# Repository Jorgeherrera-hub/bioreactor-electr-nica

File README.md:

# Proyecto mini-bioreactor electrónica biomédica

Este proyecto consiste en desarrollar un mini-biorreactor educativo de bajo costo, entendido como un sistema de cultivo a pequeña escala que permite estudiar y simular condiciones controladas de un proceso biológico. Debido a su finalidad educativa, el sistema trabajará exclusivamente con agua u otras mezclas inocuas, sin cultivar microorganismos. El proyecto busca representar, de manera sencilla y segura, el funcionamiento general de un biorreactor mediante la regulación de las condiciones del recipiente, el monitoreo de su comportamiento y teniendo como variable regulada, la temperatura del fluido.

Este proyecto contiene una placa electrónica de control para un mini biorreactor. Su elemento principal es una placa de desarrollo Arduino nano D3, que ejecuta el programa de control y recibe las señales de los sensores.

La electrónica se alimenta con una fuente de 12 V. Un diodo Schottky protege la entrada frente a inversión de polaridad; un regulador convierte los 12 V a 5 V para alimentar la placa y la pantalla, y otro regulador genera 3,3 V para los sensores y las señales de control.

Un MOSFET IRLZ44N permite regular la velocidad de un motor de corriente continua mediante una señal PWM del ESP32. Un diodo de protección y un condensador ayudan a reducir los picos eléctricos producidos por el motor. La placa también incorpora conectores para un sensor de temperatura DS18B20 y un sensor Hall de RPM, además de resistencias de polarización para sus señales.

Para la interfaz, hay un conector para una pantalla LCD 16×2 con comunicación I²C. Un adaptador de nivel con transistores BSS138 permite comunicar las señales I²C de 3,3 V del arduino con una pantalla que funciona a 5 V. También hay un conector de programación USB-UART y pulsadores para encendido/apagado, regulación, reinicio y modo de carga del arduino.

En conjunto, la electrónica permite controlar el motor y reunir las lecturas de temperatura y velocidad de giro para supervisar el funcionamiento del mini biorreactor.

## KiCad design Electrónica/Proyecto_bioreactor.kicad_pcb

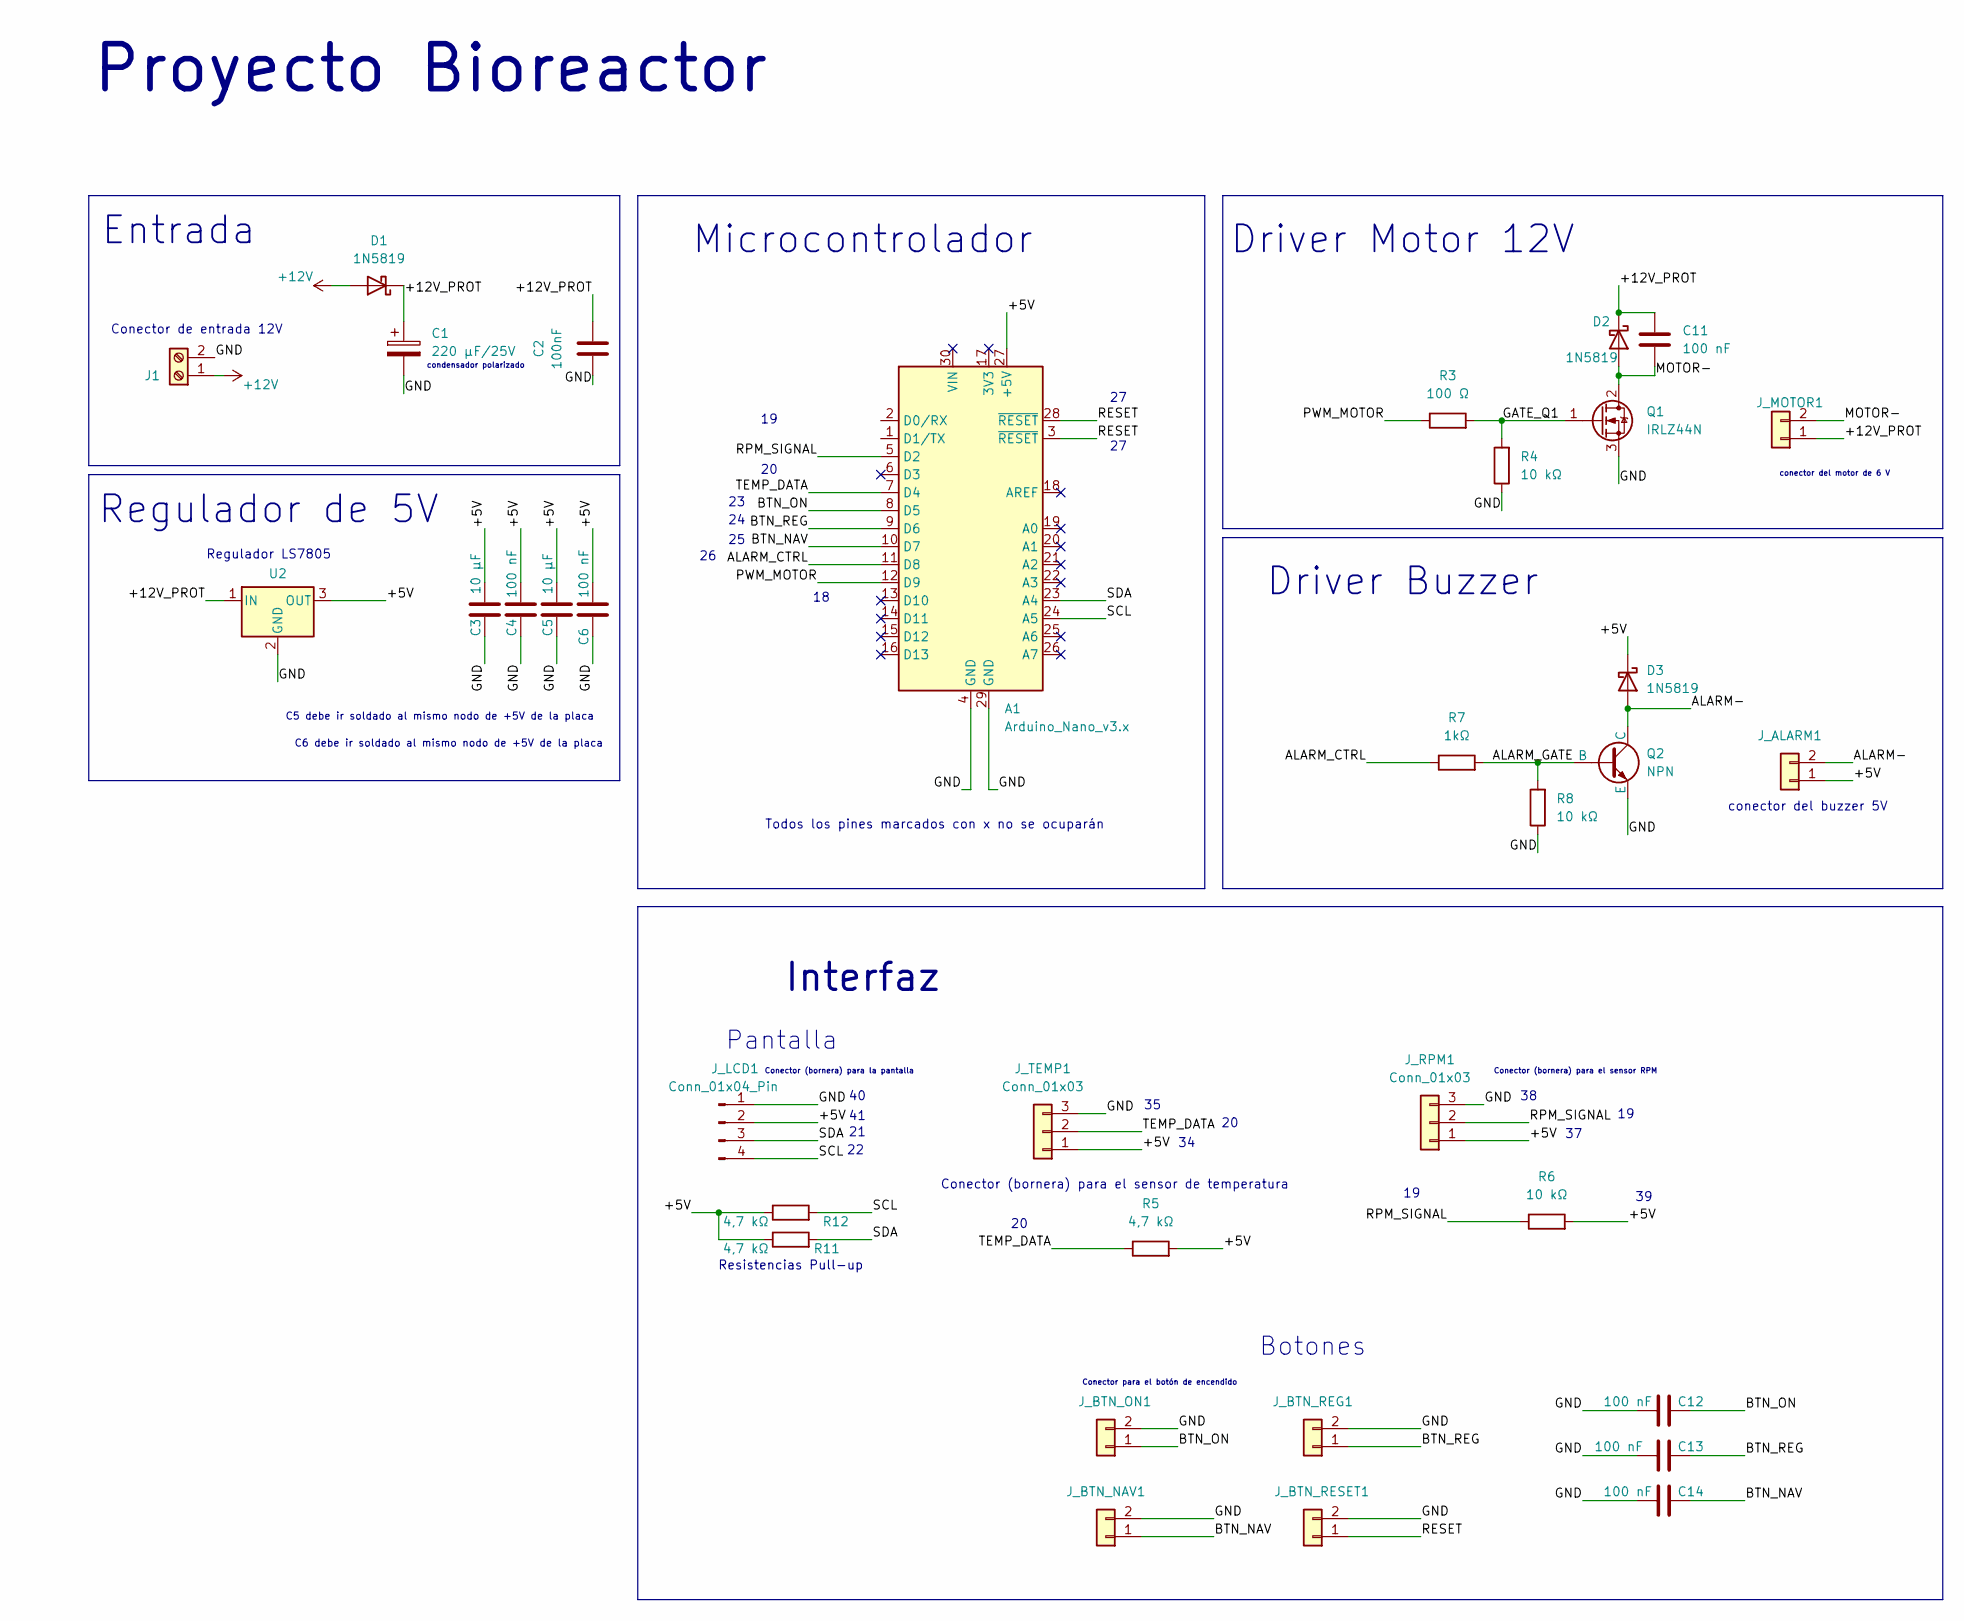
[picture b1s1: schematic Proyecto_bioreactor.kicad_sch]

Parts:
A1: Arduino_Nano_v3.x; Arduino_Nano
C1: 220 µF/25V; CP_Radial_D8.0mm_P3.50mm
C2: 100nF; C_Disc_D5.0mm_W2.5mm_P5.00mm
C3, C5: 10 µF; CP_Radial_D5.0mm_P2.00mm
C4, C6, C11, C12, C13, C14: 100 nF; C_Disc_D5.0mm_W2.5mm_P5.00mm
D1, D2, D3: 1N5819; D_DO-41_SOD81_P10.16mm_Horizontal
J1: Screw_Terminal_01x02; TerminalBlock_Phoenix_MKDS-1,5-2-5.08_1x02_P5.08mm_Horizont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
J_ALARM1: PinHeader_1x02_P2.54mm_Vertical
J_BTN_NAV1: PinHeader_1x02_P2.54mm_Vertical
J_BTN_ON1: PinHeader_1x02_P2.54mm_Vertical
J_BTN_REG1: PinHeader_1x02_P2.54mm_Vertical
J_BTN_RESET1: PinHeader_1x02_P2.54mm_Vertical
J_LCD1: Conn_01x04_Pin; PinHeader_1x04_P2.54mm_Vertical
J_MOTOR1: PinHeader_1x02_P2.54mm_Vertical; TerminalBlock_Phoenix_MKDS-1,5-2-5.08_1x02_P5.08mm_Horizont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
J_RPM1: Conn_01x03; PinHeader_1x03_P2.54mm_Vertical
J_TEMP1: Conn_01x03; PinHeader_1x03_P2.54mm_Vertical
Q1: IRLZ44N; TO-220-3_Vertical
Q2: NPN; TO-92
R3: 100 Ω; R_Axial_DIN0204_L3.6mm_D1.6mm_P7.62mm_Horizontal
R4, R6, R8: 10 kΩ; R_Axial_DIN0204_L3.6mm_D1.6mm_P7.62mm_Horizontal
R5, R11, R12: 4,7 kΩ; R_Axial_DIN0204_L3.6mm_D1.6mm_P7.62mm_Horizontal
R7: 1kΩ; R_Axial_DIN0204_L3.6mm_D1.6mm_P7.62mm_Horizontal
U2: OKI-78SR-5/1.5-W36-C (L7805); Converter_DCDC_Murata_OKI-78SR_Vertical

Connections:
+12V: D1.2 (A), J1.1
/+5V: A1.27 (+5V), C3.1, C4.1, C5.1, C6.1, D3.1 (K), J_ALARM1.1, J_LCD1.2, J_RPM1.1, J_TEMP1.1, R5.2, R6.2, R11.1, R12.1, U2.3 (OUT)
/+12V_PROT: C1.1, C2.2, C11.1, D1.1 (K), D2.1 (K), J_MOTOR1.1, U2.1 (IN)
/ALARM-: D3.2 (A), J_ALARM1.2, Q2.3 (C)
/ALARM_CTRL: A1.11 (D8), R7.1
/ALARM_GATE: Q2.2 (B), R7.2, R8.2
/BTN_NAV: A1.10 (D7), J_BTN_NAV1.1
/BTN_NAV: C14.1
/BTN_ON: A1.8 (D5), C12.1, J_BTN_ON1.1
/BTN_REG: A1.9 (D6), J_BTN_REG1.1
/BTN_REG: C13.1
/GATE_Q1: Q1.1 (G), R3.2, R4.2
/GND: A1.4 (GND), A1.29 (GND), C1.2, C2.1, C3.2, C4.2, C5.2, C6.2, C12.2, C13.2, C14.2, J1.2, J_BTN_NAV1.2, J_BTN_ON1.2, J_BTN_REG1.2, J_BTN_RESET1.2, J_LCD1.1, J_RPM1.3, J_TEMP1.3, Q1.3 (S), Q2.1 (E), R4.1, R8.1, U2.2 (GND)
/MOTOR-: C11.2, D2.2 (A), J_MOTOR1.2, Q1.2 (D)
/PWM_MOTOR: A1.12 (D9), R3.1
/RESET: A1.3 (~RESET), A1.28 (~RESET), J_BTN_RESET1.1
/RPM_SIGNAL: A1.5 (D2), J_RPM1.2, R6.1
/SCL: A1.24 (A5), J_LCD1.4, R12.2
/SDA: A1.23 (A4), J_LCD1.3, R11.2
/TEMP_DATA: A1.7 (D4), J_TEMP1.2, R5.1

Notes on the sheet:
Conector (bornera) para el sensor RPM
C6 debe ir soldado al mismo nodo de +5V de la placa
Pantalla
conector del buzzer 5V
Regulador de 5V
Conector de entrada 12V
Todos los pines marcados con x no se ocuparán
Conector para el botón de encendido
condensador polarizado
Driver Buzzer
Conector (bornera) para el sensor de temperatura
conector del motor de 6 V
Regulador LS7805
Botones
Interfaz
Proyecto Bioreactor
Resistencias Pull-up
Microcontrolador
Driver Motor 12V
Entrada
C5 debe ir soldado al mismo nodo de +5V de la placa
Conector (bornera) para la pantalla

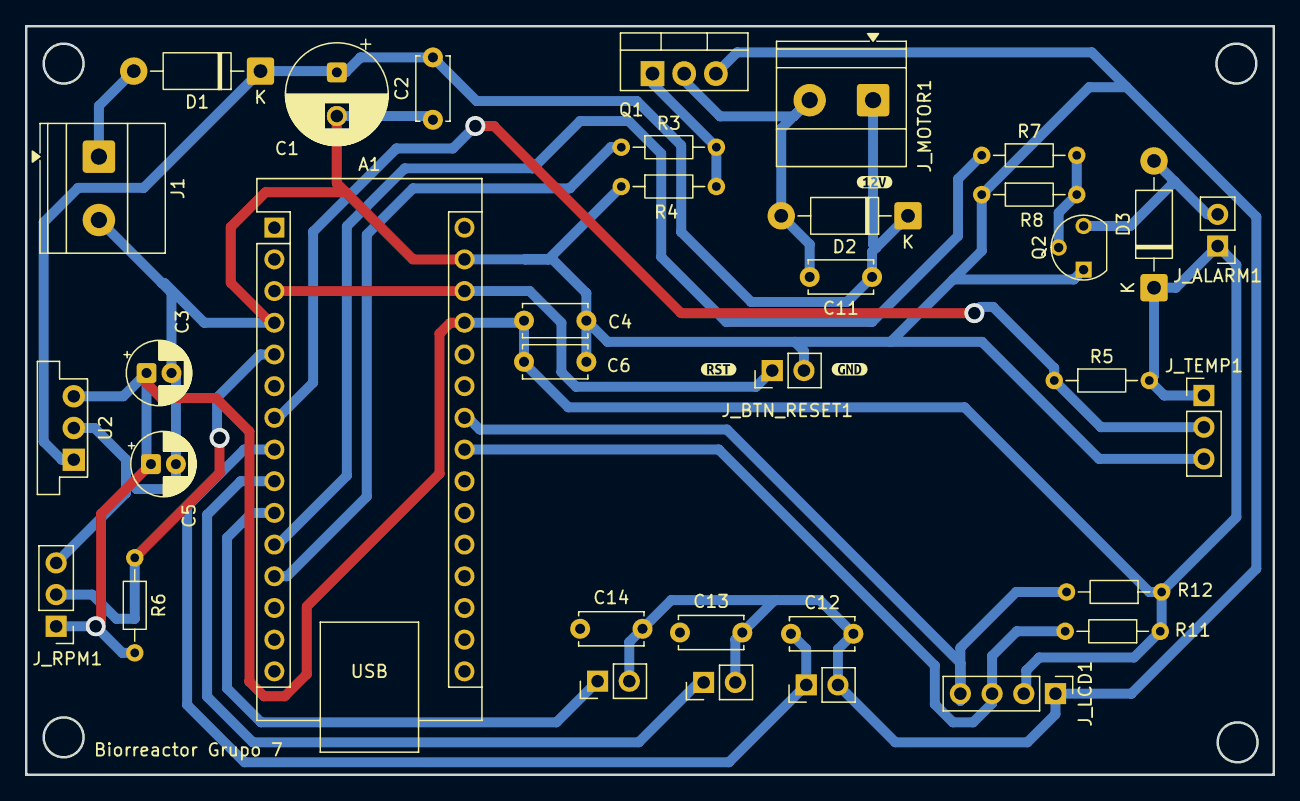
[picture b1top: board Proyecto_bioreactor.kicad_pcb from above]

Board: 2 copper layers, 100.0 x 60.0 mm, 38 parts (0 on the bottom side), 18 nets.

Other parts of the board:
kibuzzard-6AE48D6D: G***; kibuzzard-6AE48D6D
kibuzzard-6AE48D38: G***; kibuzzard-6AE48D38
kibuzzard-6AE49500: G***; kibuzzard-6AE49500
